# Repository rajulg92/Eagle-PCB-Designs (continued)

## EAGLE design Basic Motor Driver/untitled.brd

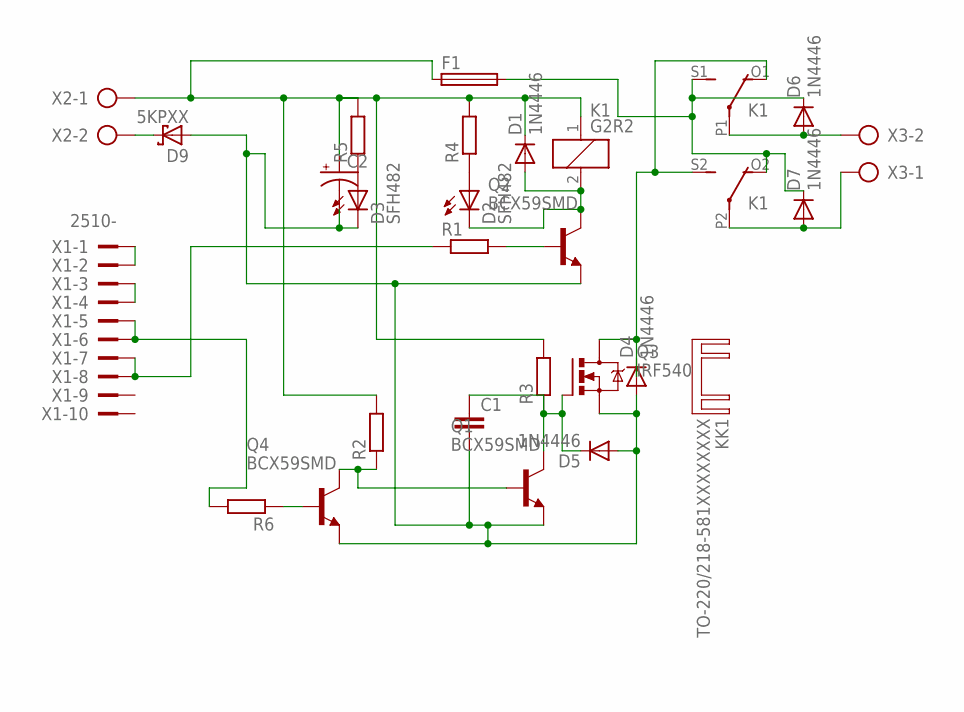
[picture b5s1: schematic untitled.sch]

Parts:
C1: C5/3; C5B3
C2: CPOL-USE7.5-16; E7,5-16
D1, D4, D5, D6, D7: 1N4446; DO35-10
D2, D3: SFH482
D9: 5KPXX; P6T15
F1: SH22,5; MPN 0031.8201
K1: G2R2
KK1: TO-220/218-581XXXXXXXX; 581XXXXXXXX
Q1, Q2, Q4: BCX59SMD; TO92-EBC
Q3: IRF540; TO220BV
R1, R2, R3, R4, R5, R6: R-EU_0207/10; 0207/10
X1: 2510-; PAK100/2500-10
X2, X3: AK300/2

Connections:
unnamed: X1.1, X1.2
unnamed: X1.3, X1.4
unnamed: R6.2, X1.5, X1.6
unnamed: R1.1, X1.7, X1.8
unnamed: D1.A, D2.K (C), K1.2, Q2.C
unnamed: Q1.B, Q4.C, R2.1
unnamed: C1.2, C2.-, D3.K (C), D4.A, D5.A, D9.A, Q1.E, Q2.E, Q3.S, Q4.E
unnamed: C2.+, D1.C, F1.1, K1.1, R2.2, R3.2, R4.2, R5.2, X2.1
unnamed: C1.1, D5.C, Q1.C, Q3.G, R3.1
unnamed: Q2.B, R1.2
unnamed: D3.A, R5.1
unnamed: D6.A, K1.P1, X3.2
unnamed: D7.A, K1.P2, X3.1
unnamed: D9.C, X2.2
unnamed: D6.C, D7.C, F1.2, K1.O2 (O), K1.S1 (S)
unnamed: D2.A, R4.1
unnamed: D4.C, K1.O1 (O), K1.S2 (S), Q3.D
unnamed: Q4.B, R6.1

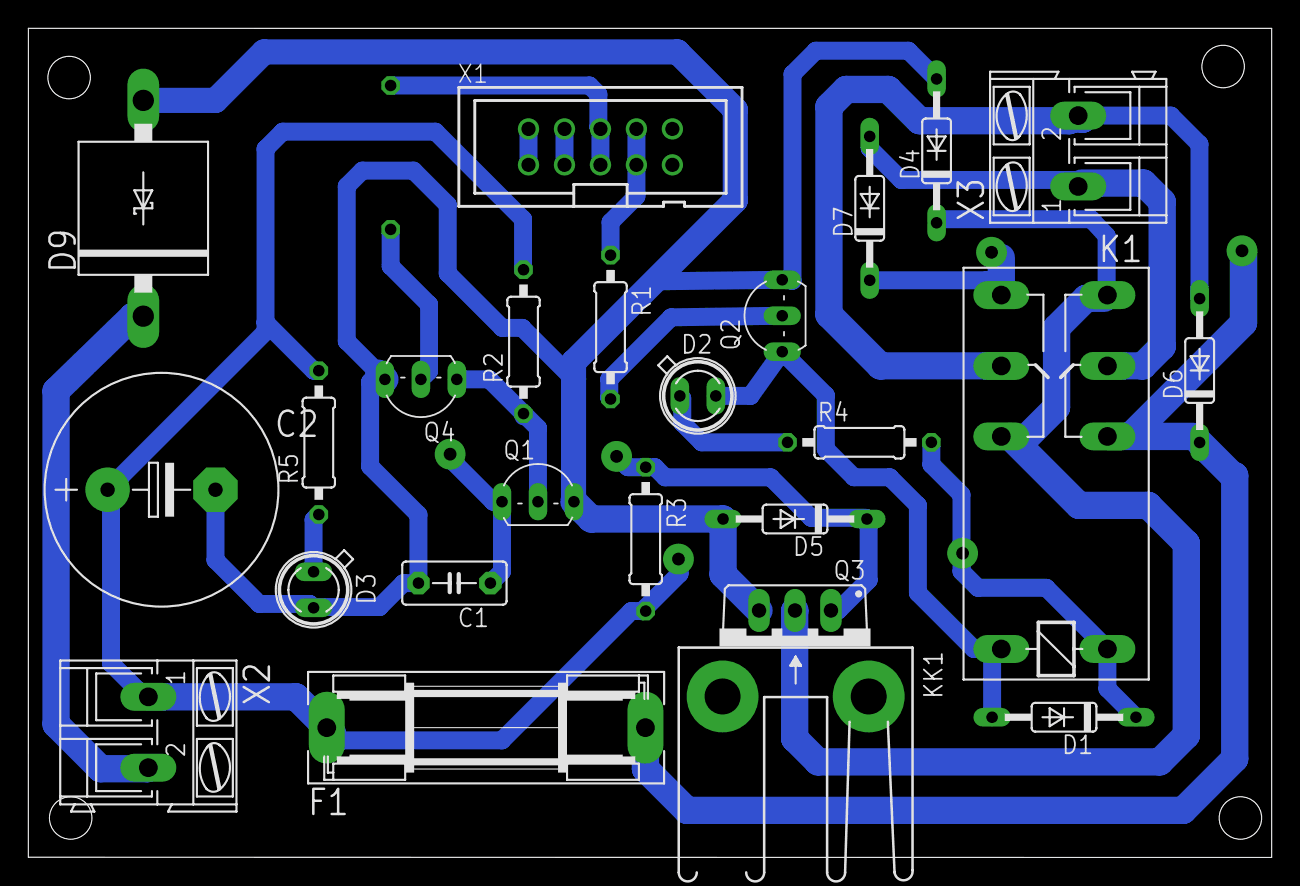
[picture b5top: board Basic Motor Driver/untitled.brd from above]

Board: 2 copper layers, 87.8 x 58.6 mm, 26 parts (1 on the bottom side), 18 nets.
